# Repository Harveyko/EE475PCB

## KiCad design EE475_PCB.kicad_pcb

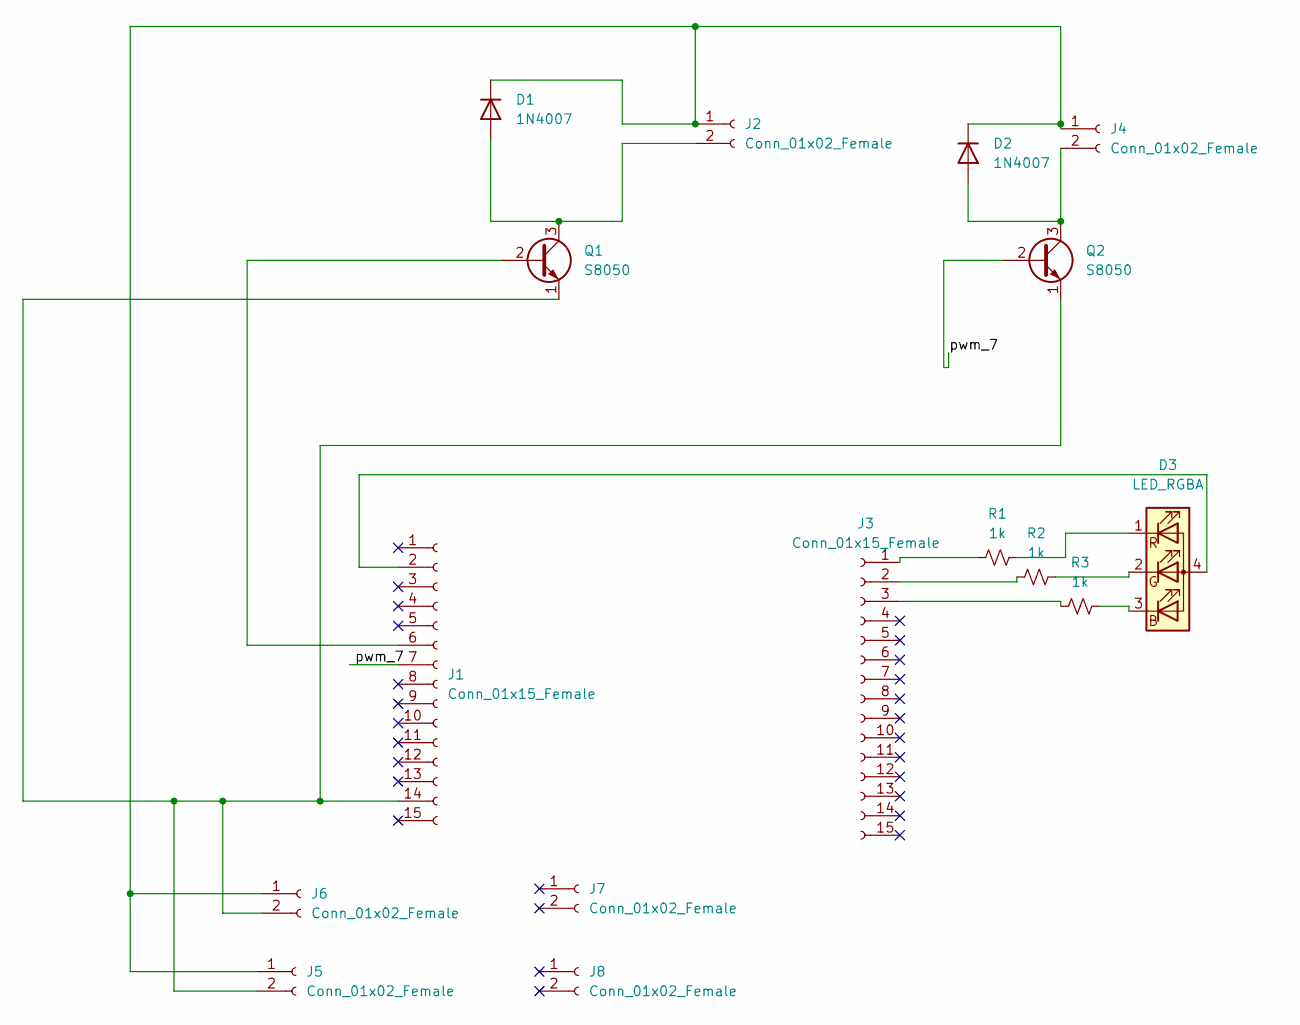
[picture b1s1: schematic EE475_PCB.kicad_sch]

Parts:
D1, D2: 1N4007; D_DO-41_SOD81_P10.16mm_Horizontal
D3: LED_RGBA; LED_RGB_1210
J1, J3: Conn_01x15_Female; PinSocket_1x15_P2.54mm_Vertical
J2, J4, J5, J6, J7, J8: Conn_01x02_Female; PinSocket_1x02_P2.54mm_Vertical
Q1, Q2: S8050; TO-92_Inline
R1, R2, R3: 1k; R_1206_3216Metric

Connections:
/pwm_7: J1.7, Q2.2 (B)
unnamed: D1.1 (K), D2.1 (K), J2.1, J4.1, J5.1, J6.1
unnamed: D1.2 (A), J2.2, Q1.3 (C)
unnamed: D2.2 (A), J4.2, Q2.3 (C)
unnamed: D3.4 (A), J1.2
unnamed: J1.6, Q1.2 (B)
unnamed: J1.14, J5.2, J6.2, Q1.1 (E), Q2.1 (E)
unnamed: J3.1, R1.2
unnamed: J3.2, R2.2
unnamed: J3.3, R3.2
unnamed: D3.1 (RK), R1.1
unnamed: D3.2 (GK), R2.1
unnamed: D3.3 (BK), R3.1

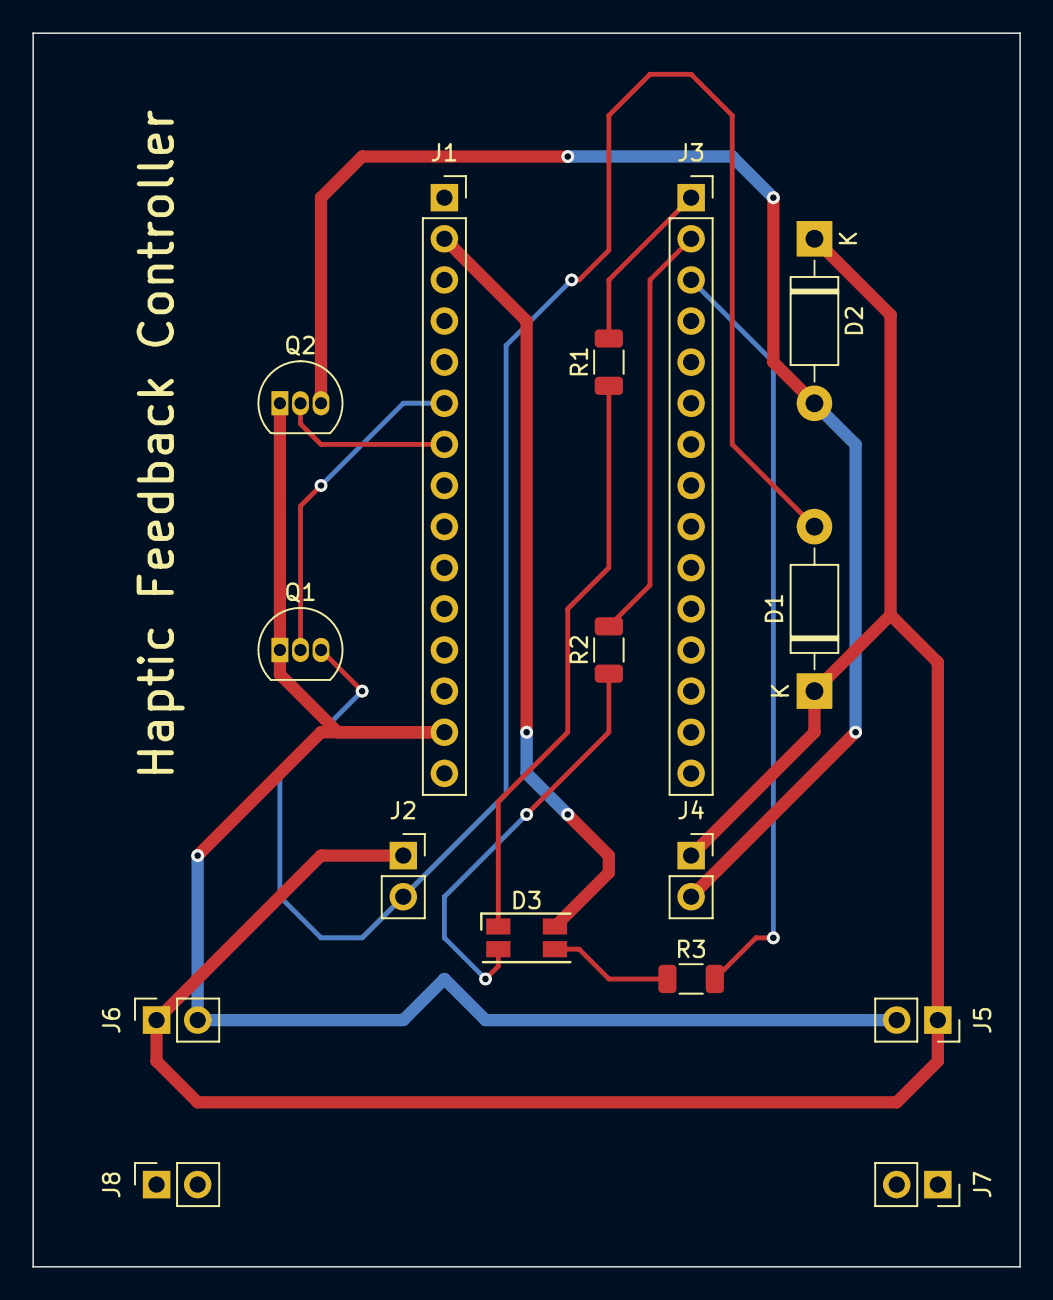
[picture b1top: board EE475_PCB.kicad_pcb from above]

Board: 2 copper layers, 61.0 x 76.2 mm, 16 parts (0 on the bottom side), 13 nets.

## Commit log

2022-10-31 Initialize git repo
2022-10-31 ensure updated
2022-10-31 add new symbol and footprint library
2022-10-31 include libraries folder
2022-10-31 Added radio module, step down converter, and labels
2022-11-01 Update some element's orientation
2022-11-04 Updated Schematic for the PCB. Removed the original parts for microcontroller based PCB
2022-11-10 Motor Controller Hub PCB Design Update. Added new schematic and layout
2022-11-11 Updated Schematic of motor hub with power supply width
2022-11-15 Final design of the PCB baord for Motor Controller
2022-11-16 Updated version of the PCB based on professor and TAs feedback
2022-11-18 Modify LED and resistor footprint
